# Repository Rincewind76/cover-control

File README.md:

# Starting Setup
I have the following equipment:
* WandererCover V4-EC Professional Flatpanel
* Celestron EdgeHD 800 with 0.7 reducer and Off-Axis-Guide and a Dew Heater
* ASIAir Plus
* ZWO ASI585MC (main) and ZWO ASI220M (Guide)
* ZWO Autofocuser
* ZWO Filter Wheel
* Sky Watcher EQ6-R Pro

So all equipment can be conviniently controlled by the ASIAir Plus, except the Wanderer Cover...
(To be fair: The Cover can be controlled by a series of power on/off cycles via the ASIAir - but this is a more a pain, than a feature)
I have a small Windows Tablet to control it - but this is overkill, just to open/close the cover and adjust the brightness.

So target of this project is to have a small standalone unit to control everything onsite via local controls (e.g. buttons)

---

# Requirements Collection

- Small controller with Wi-Fi capability to host a web interface
- USB host capability to control the WandererCover via USB virtual COM port  
  - Direct USB connection from the control system to the WandererCover
- Power supply via 12V  
  - The WandererCover is powered and switched through the control system
- Two additional separate 12V outputs, PWM-controlled  
  - For external dew heaters
- Ability to measure voltage level at the 12V input port
- Integrated temperature and humidity sensor
- Separate buttons:
  - Open
  - Close
  - Light on with a selected brightness via Poti
  - Light off
- LED feedback:
  - Light on/off status
  - Wi-Fi connection
  - USB communication feedback
- Optional: OLED support for a 0.96" display  
- Wi-Fi networks configurable via settings  
  - The strongest configured network should be used

---

# Key Components

- Wemos LOLIN S3 Pro
- Brightness adjustable via potentiometer
- BME280 climate sensor via I2C
- OLED AZDelivery SSD1306 0.96" display via I2C
- MOSFET IRLZ44N
- Buck converter 1584EN module

---

# The result - Hardware
I created the schematic and PCB in Kicad.  All files stored in subfolder hardware, there you can also find the gerber files.
Since I am not very good at soldering, therefore the design has only big components, no SMD. To keep it simple, I only wanted a single sided PCB, no Vias, no connections on top layer necessary.
There is only one palce, where sections of the ground plane is connected via the switches - but this seems to be the case in all switches of this form factor.

As I have a Carvera Air desktop CNC, I made the PCB by myself - the results are below

and the final assembled version looks like this:

After a short check, nothing seems to burn or explode after applying 12V - I went for the next part: software

A small hint: the buck converter is not fixed to 5V - so I recommend to solder that one first, then apply 12V and adjust the poti on the buck converter to get the desired 5V out of it, only then continue with the rest of the components. Otherwise there is the risk to damage components if they see more than the 5V.

# The result - Software
In case you want to adapt the software, just install Visual Studio Code with the PlatformIO extension. The rest gets downloaded automatically if you open the folder in VS Code.
The Lolin S3 Pro has only one USB port - so after the first flashing of the software you cannot use the USB port anymore for updating or logging of events.
All further updates have to be applied via the OTA method, or by manually bringing the ESP32 in the bootloader mode.

The software itself is pretty straight forward. For PIN, WiFi and I2C control you can use standard libraries.

I implemented a scheduler. It gets the time from the internet and can execute certain tasks at a predefined time. Currently I only use it for auto-closing the cover at a certain time in the morning.

First challenge is the serial communication to the cover: Unfortunately I figured out quite late, the the cover uses a CH341 chip - which does not follow the standard CDC communication. Luckily Bert Melis has developed a library to communicate with this chipset. I installed a retry mechanism: after 5s without proper communication it just re-initializes the communication.

The BME280 and OLED display have standard libraries from Adafruit - I just included them.

The Dew heater control is fully automatic, you can specify a maximum rate (usually 70%), then as soon as the temperature goes towards the dew point, the heaters gradually switch on until max power.
Two dew heaters with 12V specification can be attached, in my case I have one for the optics and one at the mount.

The Webserver is based on the ASyncWebserver libraries - quite simple but effective. 

The main page looks like this and can be accessed by http://(-IP of Cover Control-)/ :

All necessary information is stored there and updated each 2 seconds.

As mentioned before, the logging feature is no longer available via USB due to the communication to the cover, therefore you can access the logged events via the route http://(-IP of Cover Control-)/log

I found it as a pleasant surprise, that the LOLIN S3 Pro has a SD-card reader onboard - so all the configuration is stored in a textfile "config.txt" on the SD-card. The initial version is part of this repository. It can also be updated via Web-Interface - no need to get off the couch ;)

Adress to this page is http://(-IP of Cover Control-)/config

As you can see, you can define some basic behaviour - and also access data to WiFi networks (max 10). It automatically selects the strongest network and connects to this - including retry, in case connection gets lost. The format ist quite simple: `wifi=SSID;password` - each wifi network gets a new line. On this page you can also scan for networks to find the strongest one.

The `ota_password=password` is also quite important - this has to match the entry in the platformIO.ini

All in all the software is still below 1MB Flash - so plenty of headroom for more improvements.

# The result - including housing
OK - for the housing my patience was already quite low - so it does not win any beauty prices...

But it is functional - please note, that the temperature sensor is physically separated from the rest of the electronics, so that any heating of components does not affect (too much) the measurement of the surrounding temperature.

The OLED display was initially only a optional feature, but actually I do most of the adjustments with the information provided there:

# In the end
I have used this device now for several nights - no problem discovered.

You can freely use this project for your needs (as long as it is non commercial). You have all necessary information here:
- KiCad Project files with schematic and PCB layout
- Exported Gerber Files with bottom layer, top silkscreen, edge cuts and drill files
- CNC files for Makera Carvera Air (or compatible)
- 3MF Files for housing - including the source f3D file for Fusion360
- All Software files incuding platformIO.ini to build the executable

Have fun and clear skies!

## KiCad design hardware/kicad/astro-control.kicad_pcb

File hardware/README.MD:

# PIN Belegung Lolin S3 Pro:

| PIN    | Name       | Type          | Function |
| ---    | ----       | --------      | --------- |
| GPIO1  | POT_LIGHT  | Analog in     | Potentiometer for Light Intensity (50kOhm) |
| GPIO2  | LED_STATUS | Digital Out   | Control of Status LED |
| GPIO18 | LED_WLAN | Digital Out   | Control of WiFi LED |
| GPIO8  | LED_LIGHT | Digital Out   | Control of Light LED |
| GPIO42 | BTN_OPEN   | Input Pullup  | Switch input Open Cover, needs software debounce |
| GPIO41 | BTN_CLOSE  | Input Pullup  | Switch input Close Cover, needs software debounce |
| GPIO40 | BTN_LIGHT_ON  | Input Pullup  | Switch input Light on, needs software debounce |
| GPIO39 | BTN_LIGHT_OFF  | Input Pullup  | Switch input Light off, needs software debounce |
| GPIO5  | DEW1_OUT | Digital Out   | Enable DEW1 Heater 12V Supply, PWM |
| GPIO7  | DEW2_OUT | Digital Out   | Enable DEW2 Heater 12V Supply, PWM |
| GPIO16  | PAN_OUT | Digital Out   | Enable Flat Panel 12V Supply |
| GPIO4  | VIN_12V_SENSE  | Analog in     | Supply Voltage monitor, voltage divider with 100kOhm and 22kOhm |
| GPIO13  | SD_MISO  | SPI MISO     | SPI for SD-Card, MISO |
| GPIO12 | SD_SCK  | SPI CLK     | SPI for SD-Card, CLK |
| GPIO11 | SD_MOSI  | SPI MOSI     | SPI for SD-Card, MOSI |
| GPIO46 | SD_CS  | SPI CS     | SPI for SD-Card, CS |
| GPIO19 | D-  | USB D-     | USB Host to Cover, D- |
| GPIO20 | D+  | USB D+     | USB Host to Cover, D+ |
| GPIO9 | SDA  | I2C SDA     | I2C bus, connected to BME280 Sensor (0x77) and SSD1306 0,96" OLED Display (0x3C) |
| GPIO10 | SCL  | I2C SCL    | I2C bus, connected to BME280 Sensor (0x77) and SSD1306 0,96" OLED Display (0x3C) |

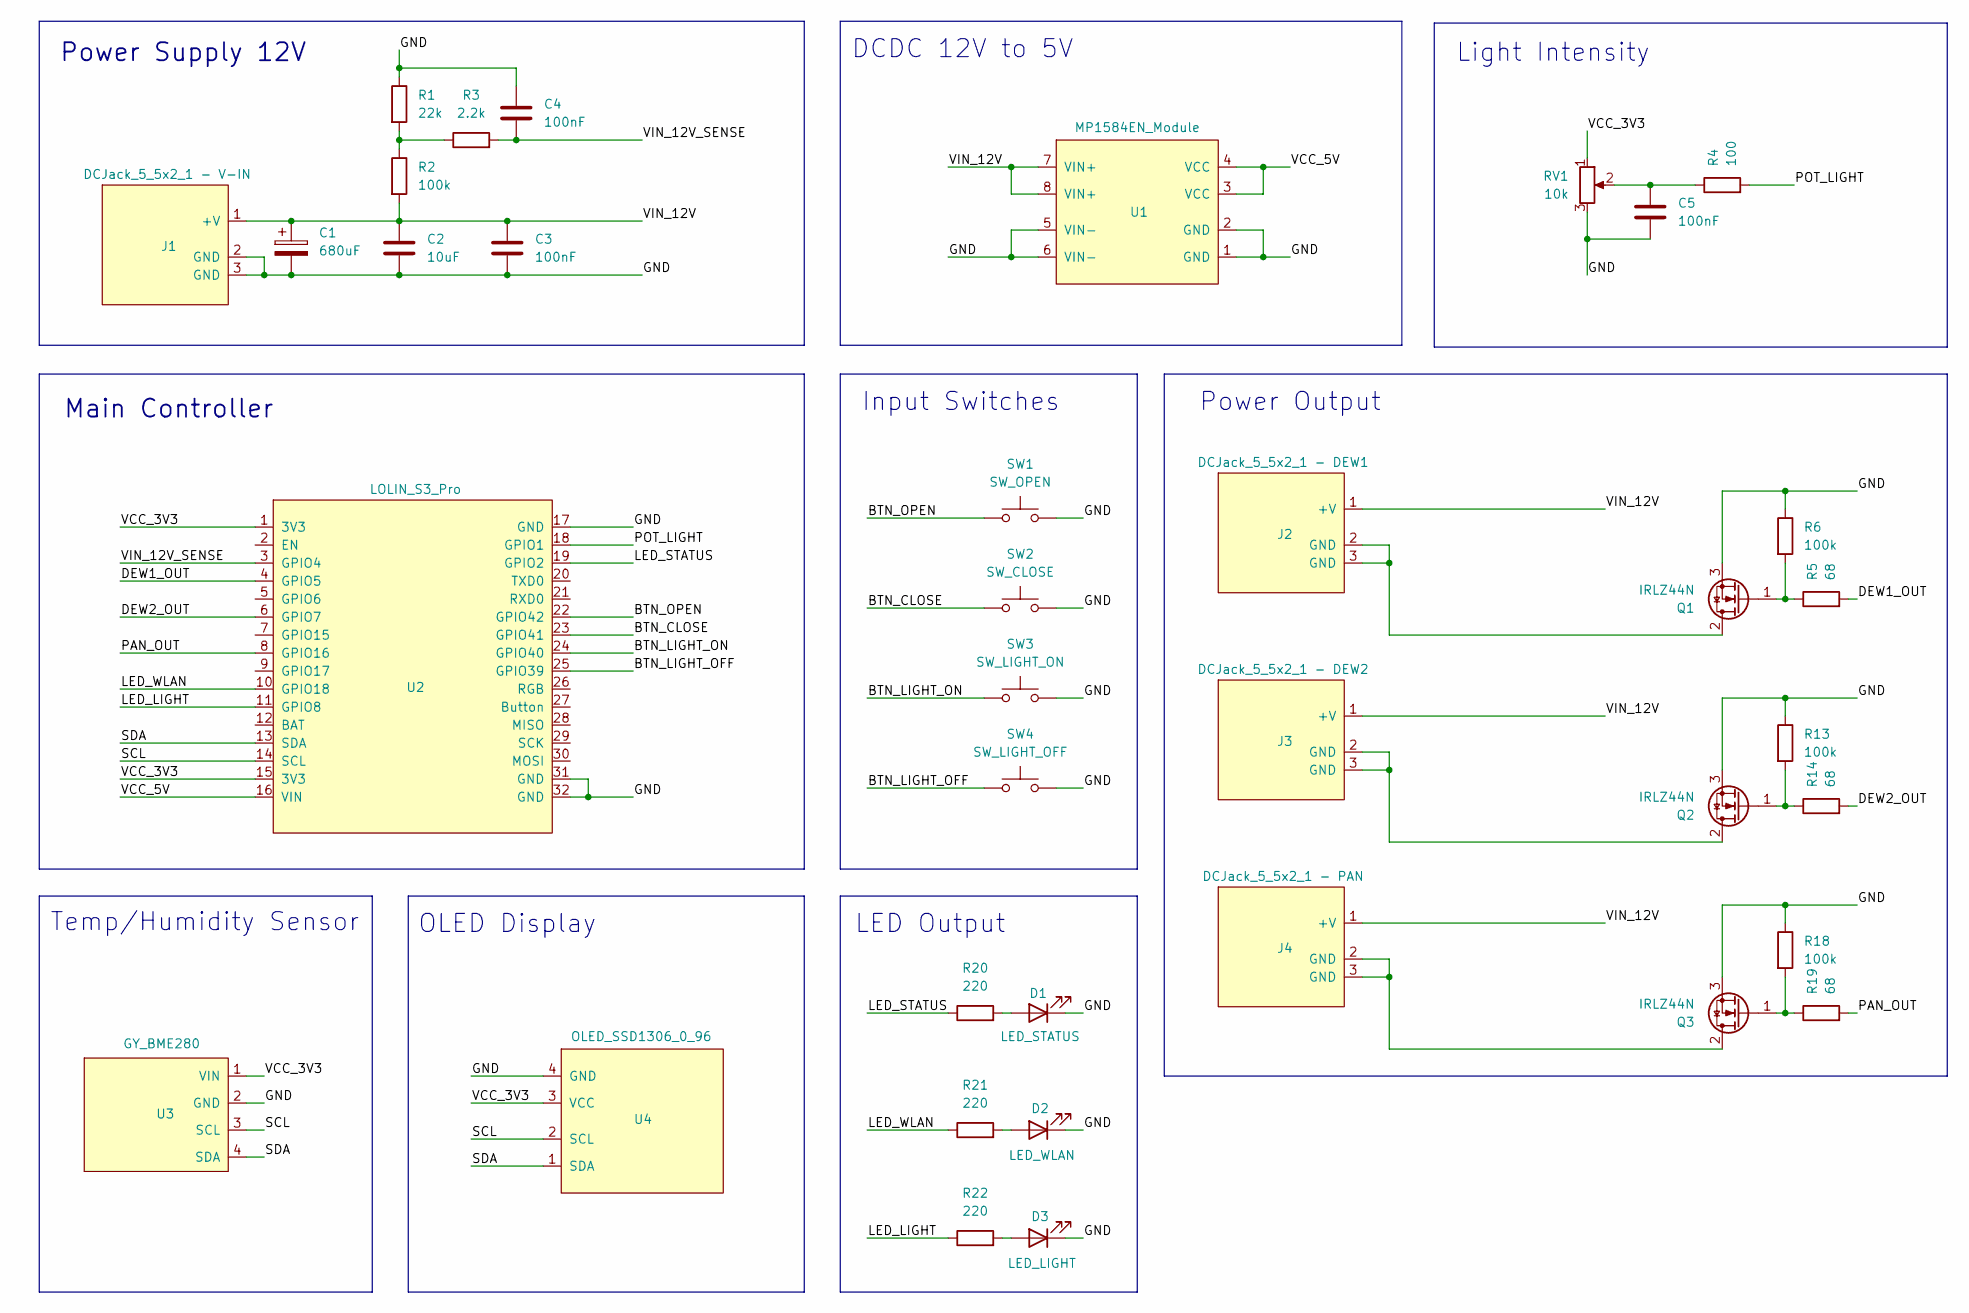
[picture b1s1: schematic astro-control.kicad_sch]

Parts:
C1: 680uF; CP_Radial_D8.0mm_P3.50mm
C2: 10uF; CP_Radial_Tantal_D5.5mm_P2.50mm
C3, C4, C5: 100nF; C_Disc_D5.1mm_W3.2mm_P5.00mm
D1: LED_STATUS; LED_D3.0mm
D2: LED_WLAN; LED_D3.0mm
D3: LED_LIGHT; LED_D3.0mm
J1: DCJack_5_5x2_1 - V-IN; DCJack_5_5x2_1_Right
J2: DCJack_5_5x2_1 - DEW1; DCJack_5_5x2_1_Right
J3: DCJack_5_5x2_1 - DEW2; DCJack_5_5x2_1_Right
J4: DCJack_5_5x2_1 - PAN; DCJack_5_5x2_1_Right
Q1, Q2, Q3: IRLZ44N; TO-220-3_Vertical
R1: 22k; R_Axial_DIN0207_L6.3mm_D2.5mm_P7.62mm_Horizontal
R2, R6, R13, R18: 100k; R_Axial_DIN0207_L6.3mm_D2.5mm_P7.62mm_Horizontal
R3: 2.2k; R_Axial_DIN0207_L6.3mm_D2.5mm_P7.62mm_Horizontal
R4: 100; R_Axial_DIN0207_L6.3mm_D2.5mm_P7.62mm_Horizontal
R5, R14, R19: 68; R_Axial_DIN0207_L6.3mm_D2.5mm_P7.62mm_Horizontal
R20, R21, R22: 220; R_Axial_DIN0207_L6.3mm_D2.5mm_P7.62mm_Horizontal
RV1: 10k; Potentiometer_Alps_RK09K_Single_Vertical
SW1: SW_OPEN; SW_PUSH_6mm_H5mm
SW2: SW_CLOSE; SW_PUSH_6mm_H5mm
SW3: SW_LIGHT_ON; SW_PUSH_6mm_H5mm
SW4: SW_LIGHT_OFF; SW_PUSH_6mm_H5mm
U1: MP1584EN_Module
U2: LOLIN_S3_Pro; LOLIN_S3_Pro_Module
U3: GY_BME280; GY_BME280_AZ_4P
U4: OLED_SSD1306_0_96; OLED_SSD1306_0v96_I2C_4P

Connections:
/BTN_CLOSE: SW2.1, U2.23 (GPIO41)
/BTN_LIGHT_OFF: SW4.1, U2.25 (GPIO39)
/BTN_LIGHT_ON: SW3.1, U2.24 (GPIO40)
/BTN_OPEN: SW1.1, U2.22 (GPIO42)
/DEW1_OUT: R5.2, U2.4 (GPIO5)
/DEW2_OUT: R14.2, U2.6 (GPIO7)
/GND: C1.2, C2.2, C3.2, C4.1, C5.2, D1.1 (K), D2.1 (K), D3.1 (K), J1.2 (GND), J1.3 (GND), Q1.3 (S), Q2.3 (S), Q3.3 (S), R1.1, R6.1, R13.1, R18.1, RV1.3, SW1.2, SW2.2, SW3.2, SW4.2, U1.1 (GND), U1.2 (GND), U1.5 (VIN-), U1.6 (VIN-), U2.17 (GND), U2.31 (GND), U2.32 (GND), U3.2 (GND), U4.4 (GND)
/LED_LIGHT: R22.1, U2.11 (GPIO8)
/LED_STATUS: R20.1, U2.19 (GPIO2)
/LED_WLAN: R21.1, U2.10 (GPIO18)
/PAN_OUT: R19.2, U2.8 (GPIO16)
/POT_LIGHT: R4.2, U2.18 (GPIO1)
/SCL: U2.14 (SCL), U3.3 (SCL), U4.2 (SCL)
/SDA: U2.13 (SDA), U3.4 (SDA), U4.1 (SDA)
/VCC_3V3: RV1.1, U2.1 (3V3), U2.15 (3V3), U3.1 (VIN), U4.3 (VCC)
/VCC_5V: U1.3 (VCC), U1.4 (VCC), U2.16 (VIN)
/VIN_12V: C1.1, C2.1, C3.1, J1.1 (+V), J2.1 (+V), J3.1 (+V), J4.1 (+V), R2.2, U1.7 (VIN+), U1.8 (VIN+)
/VIN_12V_SENSE: C4.2, R3.2, U2.3 (GPIO4)
unnamed: C5.1, R4.1, RV1.2
unnamed: D1.2 (A), R20.2
unnamed: D2.2 (A), R21.2
unnamed: D3.2 (A), R22.2
unnamed: J2.2 (GND), J2.3 (GND), Q1.2 (D)
unnamed: Q1.1 (G), R5.1, R6.2
unnamed: J3.2 (GND), J3.3 (GND), Q2.2 (D)
unnamed: Q2.1 (G), R13.2, R14.1
unnamed: J4.2 (GND), J4.3 (GND), Q3.2 (D)
unnamed: Q3.1 (G), R18.2, R19.1
unnamed: R1.2, R2.1, R3.1

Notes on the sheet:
DCDC 12V to 5V
Power Output
Light Intensity
OLED Display
Input Switches
LED Output
Power Supply 12V
Temp/Humidity Sensor
Main Controller

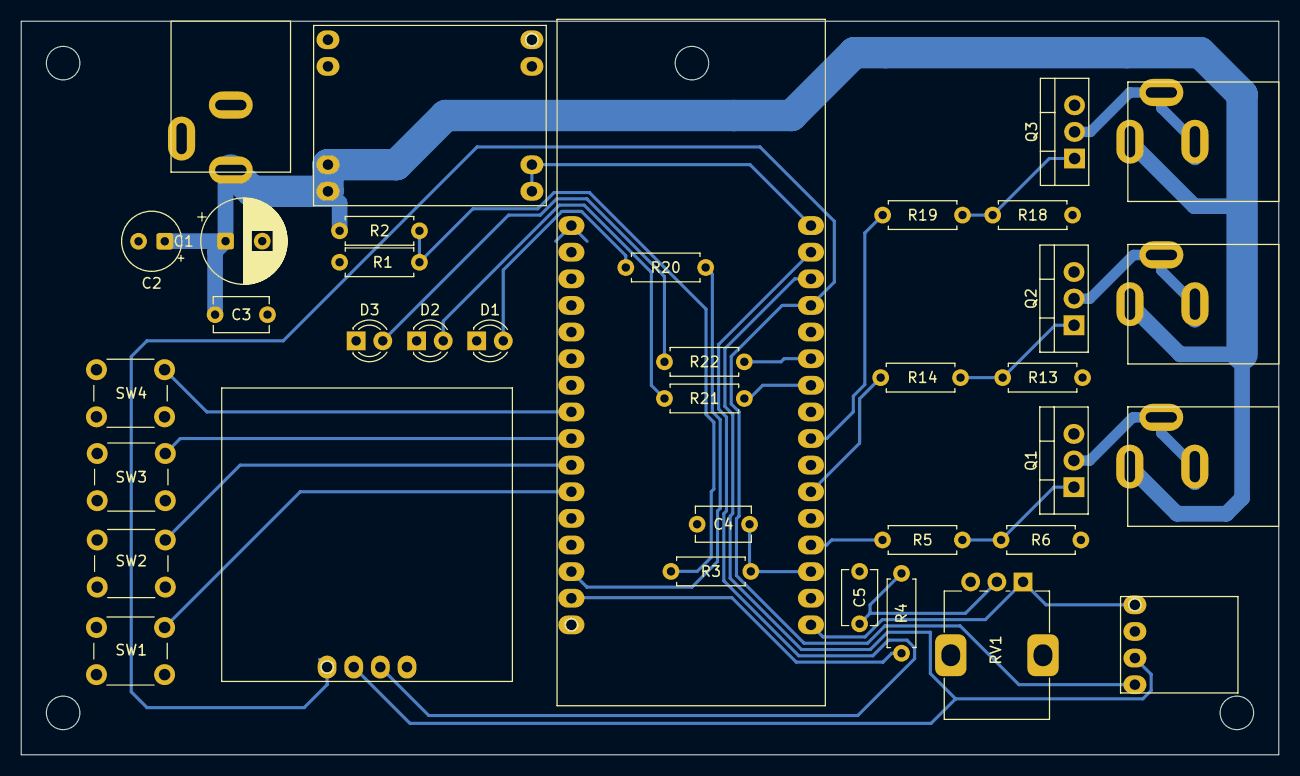
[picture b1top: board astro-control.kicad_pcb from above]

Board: 2 copper layers, 120.0 x 70.0 mm, 37 parts (0 on the bottom side), 29 nets.

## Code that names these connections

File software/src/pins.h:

#ifndef PINS_H
#define PINS_H

#include <Arduino.h>

// --- ANALOG INPUTS ---
extern const uint8_t PIN_POT_LIGHT;        // GPIO1
extern const uint8_t PIN_VIN_12V_SENSE;    // GPIO4

// --- DIGITAL OUTPUTS ---
extern const uint8_t PIN_LED_STATUS;       // GPIO2
extern const uint8_t PIN_LED_WLAN;         // GPIO18
extern const uint8_t PIN_LED_LIGHT;        // GPIO8

extern const uint8_t PIN_DEW1_OUT;         // GPIO5 (PWM)
extern const uint8_t PIN_DEW2_OUT;         // GPIO7 (PWM)
extern const uint8_t PIN_PAN_OUT;          // GPIO16

// --- BUTTON INPUTS (active low, pullup) ---
extern const uint8_t PIN_BTN_OPEN;         // GPIO42
extern const uint8_t PIN_BTN_CLOSE;        // GPIO41
extern const uint8_t PIN_BTN_LIGHT_ON;     // GPIO40
extern const uint8_t PIN_BTN_LIGHT_OFF;    // GPIO39

// --- SD CARD (SPI) ---
extern const uint8_t PIN_SD_MISO;          // GPIO13
extern const uint8_t PIN_SD_MOSI;          // GPIO11
extern const uint8_t PIN_SD_SCK;           // GPIO12
extern const uint8_t PIN_SD_CS;            // GPIO46

// --- USB HOST (WandererCover) ---
extern const uint8_t PIN_USB_D_MINUS;      // GPIO19
extern const uint8_t PIN_USB_D_PLUS;       // GPIO20

// --- I2C BUS ---
extern const uint8_t PIN_I2C_SDA;          // GPIO9
extern const uint8_t PIN_I2C_SCL;          // GPIO10

// --- INITIALIZATION ---
void initPins();

#endif

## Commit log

2026-01-12 Add LICENSE file with Creative Commons license
2026-01-15 Revise requirements section in README.md
    Updated the requirements section to include detailed specifications for the project.
2026-01-15 added manuals of Wanderer Cover
2026-01-15 added kicad files
2026-01-15 added software
2026-01-15 added housing
2026-01-15 added images of final control
2026-01-16 PCB pictures added
2026-01-16 Update README with project requirements and results
    Added requirements and detailed sections for hardware, software, and housing results.
2026-01-16 Fix image links in README.md
    Updated image links in README to use markdown syntax.
2026-01-16 Fix image markdown syntax in README.md
2026-01-16 rotated pictures
2026-01-16 Enhance README with software details and features
    Expanded the software section with details on features, libraries used, and web server functionality. Added notes on communication challenges and configuration storage.
2026-01-16 Improve README formatting and add new information
    Updated README.md for clarity and added new sections.
2026-01-16 Enhance README with WiFi and OTA password details
    Expanded explanation of WiFi configuration and OTA password.
2026-01-16 Fix image filename in README
    Updated image filename in README to reflect correct naming.
